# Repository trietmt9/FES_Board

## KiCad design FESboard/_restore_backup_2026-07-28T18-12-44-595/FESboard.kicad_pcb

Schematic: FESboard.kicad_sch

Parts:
C1, C2, C3, C4: 22nF; C_0402_1005Metric
C5, C6, C7, C8, C9, C10, C11, C12: 2.2nF; C_0402_1005Metric
C13, C15, C16, C22, C26: 10uF; C_0603_1608Metric
C14, C30, C34: 1uF; C_0603_1608Metric
C17: 22uF; C_0402_1005Metric
C18, C20, C21, C24, C32, C42, C60, C61, C62: 1uF; C_0402_1005Metric
C19, C23, C27, C29, C31: 0.1uF; C_0402_1005Metric
C25: 0.1uF; C_0603_1608Metric
C28: 3.3nF; C_0603_1608Metric
C33: 1.5nF; C_0402_1005Metric
C35: 22uF; C_0603_1608Metric_Pad1.08x0.95mm_HandSolder
C36: 4.7uF; C_0402_1005Metric
C37, C38, C39, C40, C41, C43, C44, C45, C47, C48, C49, C52, C54, C55, C56, C57, C58, C59, C63: 100nF; C_0402_1005Metric
C46, C50: 8pF; C_0402_1005Metric
C51, C53: 2.2uF; C_0402_1005Metric
C64: 47uF; C_0805_2012Metric
D1, D2, D3, D4, D5, D6, D7, D8: BAV99; SOT-23
D9, D10: LED; LED_0603_1608Metric
F1: Fuse; Fuse_0603_1608Metric
J1, J2, J3, J4: AudioJack4; Jack_3.5mm_PJ320D_Horizontal
J5: USB_C_Receptacle_USB2.0_16P; USB_C_Receptacle_GCT_USB4105-xx-A_16P_TopMnt_Horizontal
J6: Conn_01x02_Pin; JST_PH_S2B-PH-K_1x02_P2.00mm_Horizontal
J7, J8: Conn_ARM_SWD_TagConnect_TC2030-NL; Tag-Connect_TC2030-IDC-NL_2x03_P1.27mm_Vertical
L1: 2.2uH; L_0603_1608Metric
R1, R2, R3, R4: 10k; R_0603_1608Metric
R5: 30k; R_0402_1005Metric
R6, R7, R8, R9, R10, R11, R12, R13: 4.7k; R_0402_1005Metric
R14, R15, R23: 1M; R_0402_1005Metric
R16: 1.13k; R_0402_1005Metric
R17: 3.6k; R_0402_1005Metric
R18, R19: 5.1k; R_0402_1005Metric
R20, R21: 1k; R_0402_1005Metric
R22, R24, R25, R29, R30, R31, R32, R33: 10k; R_0402_1005Metric
R26, R28: 100k; R_0603_1608Metric
R27: 316k; R_0603_1608Metric
R34: 51k; R_0402_1005Metric
R35: 100k; R_0402_1005Metric
U1: BQ24074RGT; VQFN-16-1EP_3x3mm_P0.5mm_EP1.6x1.6mm
U2: ADS1298xPAG; TQFP-64_10x10mm_P0.5mm
U3: TPS62130A; VQFN-16-1EP_3x3mm_P0.5mm_EP1.68x1.68mm_ThermalVias
U4: TPS7A20xxxDBV; SOT-23-5
U5: ICM-42688-P; PQFN50P300X250X97-14N; PARTREV 1.2
U6: STM32F767ZITx; LQFP-144_20x20mm_P0.5mm
U7: WT02C40C
Y1: 8MHz; Crystal_SMD_3225-4Pin_3.2x2.5mm

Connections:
+3.3V: C31.1, C32.1, C35.1, C36.1, C37.1, C38.1, C39.1, C40.1, C41.1, C42.1, C43.1, C44.1, C45.1, C47.1, C49.1, C52.1, C54.1, C55.1, C56.1, C57.1, C58.1, C59.1, C60.1, C61.1, C62.1, C63.1, C64.1, J7.1 (VCC), J8.1 (VCC), L1.2, R24.1, R25.1, R26.1, R27.1, R29.1, R30.1, R31.1, R32.1, U2.48 (DVDD), U2.50 (DVDD), U3.14 (VOS), U5.5 (VDDIO), U5.8 (VDD), U6.6 (VBAT), U6.17 (VDD), U6.30 (VDD), U6.32 (VREF+), U6.33 (VDDA), U6.39 (VDD), U6.52 (VDD), U6.62 (VDD), U6.72 (VDD), U6.84 (VDD), U6.95 (VDDUSB), U6.108 (VDD), U6.121 (VDDSDMMC), U6.131 (VDD), U6.143 (PDR_ON), U6.144 (VDD), U7.9 (VDD), U7.17 (VBAT-3V6), U7.F4 (F4/VDDH)
+3.3VA: C24.1, C27.1, C29.2, C34.1, D1.2 (A), D2.2 (A), D3.2 (A), D4.2 (A), D5.2 (A), D6.2 (A), D7.2 (A), D8.2 (A), U2.19 (AVDD), U2.21 (AVDD), U2.22 (AVDD), U2.54 (AVDD1), U2.56 (AVDD), U2.59 (AVDD), U4.5 (OUT)
/IN1N: C1.1, C5.2, D3.3 (K), R6.2, U2.15 (IN1N)
/IN1P: C1.2, C6.1, D4.3 (K), R7.1, U2.16 (IN1P)
/IN2N: C2.1, C7.2, D1.3 (K), R8.2, U2.13 (IN2N)
/IN2P: C2.2, C8.1, D2.3 (K), R9.1, U2.14 (IN2P)
/IN3N: C3.1, C9.2, D7.3 (K), R10.2, U2.11 (IN3N)
/IN3P: C3.2, C10.1, D8.3 (K), R11.1, U2.12 (IN3P)
/IN4N: C4.1, C11.2, D5.3 (K), R12.2, U2.9 (IN4N)
/IN4P: C4.2, C12.1, D6.3 (K), R13.1, U2.10 (IN4P)
/OSC_IN: C46.1, U6.23 (PH0), Y1.1
/OSC_OUT: C50.1, U6.24 (PH1), Y1.3
/RLDOUT: C33.2, R1.2, R2.2, R3.2, R4.2, R23.2, U2.62 (RLDIN), U2.63 (RLDOUT)
/STM32_ADS_START: R25.2, U2.38 (START), U6.47 (PB1)
/STM32_IMU_INT1: U5.4 (INT1/INT), U6.73 (PB12)
/STM32_IMU_INT2: U5.9 (INT2/FSYNC/CLKIN), U6.78 (PD9)
/STM32_MISO: U2.43 (DOUT), U6.42 (PA6)
/STM32_MOSI: U2.34 (DIN), U6.43 (PA7)
/STM32_NRF_UART_RX: U6.37 (PA3), U7.11 (P009)
/STM32_NRF_UART_TX: U6.36 (PA2), U7.12 (P011)
/STM32_SCLK: U2.40 (SCLK), U6.41 (PA5)
/STM32_SPI2_MISO: U5.1 (AP_SDO/AP_AD0), U6.75 (PB14)
/STM32_SPI2_MOSI: U5.14 (AP_SDA/AP_SDIO/AP_SDI), U6.76 (PB15)
/STM32_SPI2_SCK: U5.13 (AP_SCL/AP_SCLK), U6.74 (PB13)
/SWCLK: J8.4 (SWCLK), U6.109 (PA14)
/SWDIO: J8.2 (SWDIO), U6.105 (PA13)
/USB_DN: J5.A7 (D-), J5.B7 (D-), U6.103 (PA11)
/USB_DP: J5.A6 (D+), J5.B6 (D+), U6.104 (PA12)
/~RST: C48.1, J8.3 (~RESET), R32.2, U6.25 (NRST)
/~STM32_ADS_CS: U2.39 (~CS), U6.40 (PA4)
/~STM32_ADS_DRDY: R29.2, U2.47 (~DRDY), U6.44 (PC4)
/~STM32_ADS_PWDWN: R30.2, U2.35 (~PWDN), U6.45 (PC5)
/~STM32_ADS_RESET: R31.2, U2.36 (~RESET), U6.46 (PB0)
/~STM32_IMU_CS: U5.12 (AP_CS), U6.77 (PD8)
GND: C13.2, C14.2, C15.2, C16.2, C17.2, C18.2, C19.2, C20.2, C21.2, C22.2, C25.2, C28.2, C31.2, C32.2, C35.2, C36.2, C37.2, C38.2, C39.2, C40.2, C41.2, C42.2, C43.2, C44.2, C45.2, C46.2, C47.2, C48.2, C49.2, C50.2, C51.2, C52.2, C53.2, C54.2, C55.2, C56.2, C57.2, C58.2, C59.2, C60.2, C61.2, C62.2, C63.2, C64.2, J5.A1 (GND), J5.A12 (GND), J5.B1 (GND), J5.B12 (GND), J5.SH (SHIELD), J6.1, J7.5 (GND), J8.5 (GND), R5.1, R14.1, R16.1, R17.1, R18.1, R19.1, R22.1, R28.2, R33.1, R35.2, U1.4 (~CE), U1.8 (VSS), U1.17 (VSS), U2.31 (RESV1), U2.33 (DGND), U2.41 (DAISY_IN), U2.49 (DGND), U2.51 (DGND), U3.6 (GND), U3.7 (FSW), U3.8 (DEF), U3.15 (GND), U3.16 (GND), U3.17 (GND), U5.6 (GND), U5.7 (RESV_7), U6.16 (VSS), U6.31 (VSSA), U6.38 (VSS), U6.51 (VSS), U6.61 (VSS), U6.83 (VSS), U6.94 (VSS), U6.107 (VSS), U6.120 (VSS), U6.130 (VSS), U7.10 (GND), U7.A0 (A0/VSS1), U7.B0 (B0/VSS2), U7.C0 (C0/VSS3), U7.D0 (D0/VSS4), U7.H0 (H0/GND), U7.H1 (H1/GND), U7.H2 (H2/GND), U7.H3 (H3/GND), Y1.2 (G), Y1.4 (G)
GNDA: C5.1, C6.2, C7.1, C8.2, C9.1, C10.2, C11.1, C12.2, C23.2, C24.2, C26.2, C27.2, C29.1, C30.2, C34.2, D1.1 (K), D2.1 (K), D3.1 (K), D4.1 (K), D5.1 (K), D6.1 (K), D7.1 (K), D8.1 (K), J1.R2, J2.R2, J3.R2, J4.R2, U2.20 (AVSS), U2.23 (AVSS), U2.25 (VREFN), U2.32 (AVSS), U2.53 (AVSS1), U2.57 (AVSS), U2.58 (AVSS), U4.2 (GND)
unnamed: D9.2 (A), R20.2
unnamed: D9.1 (K), U1.9 (~CHG)
unnamed: D10.2 (A), R21.2
unnamed: D10.1 (K), U1.7 (~PGOOD)
unnamed: F1.1, J5.A4 (VBUS), J5.A9 (VBUS), J5.B4 (VBUS), J5.B9 (VBUS)
unnamed: J1.R1, R6.1
unnamed: J1.S, R1.1
unnamed: J1.T, R7.2
unnamed: J2.R1, R8.1
unnamed: J2.S, R2.1
unnamed: J2.T, R9.2
unnamed: J3.R1, R10.1
unnamed: J3.S, R3.1
unnamed: J3.T, R11.2
unnamed: J4.R1, R12.1
unnamed: J4.S, R4.1
unnamed: J4.T, R13.2
unnamed: J5.A5 (CC1), R18.2
unnamed: J5.B5 (CC2), R19.2
unnamed: C16.1, J6.2, U1.2 (BAT), U1.3 (BAT)
unnamed: J7.4 (SWCLK), U7.15 (SWCLK)
unnamed: J7.2 (SWDIO), U7.16 (SWDIO)
unnamed: J7.3 (~RESET), U7.14 (RESET)
unnamed: L1.1, U3.1 (SW), U3.2 (SW), U3.3 (SW)
unnamed: R14.2, U1.6 (EN1)
unnamed: R15.2, U1.5 (EN2)
unnamed: R16.2, U1.12 (ILIM)
unnamed: R17.2, U1.16 (ISET)
unnamed: R5.2, U1.14 (TMR)
unnamed: R22.2, U1.1 (TS)
unnamed: R24.2, U2.52 (CLKSEL)
unnamed: C33.1, R23.1, U2.61 (RLDINV)
unnamed: C17.1, U2.28 (VCAP1)
unnamed: C18.1, U2.30 (VCAP2)
unnamed: C19.1, C20.1, U2.55 (VCAP3)
unnamed: C21.1, U2.26 (VCAP4)
unnamed: C23.1, C26.1, U2.24 (VREFP)
unnamed: R27.2, R28.1, U3.5 (FB)
unnamed: R26.2, U3.4 (PG)
unnamed: C28.1, U3.9 (SS/TR)
unnamed: R33.2, U6.138 (BOOT0)
unnamed: R34.2, R35.1, U6.101 (PA9)
unnamed: C51.1, U6.71 (VCAP_1)
unnamed: C53.1, U6.106 (VCAP_2)
VBUS: C13.1, C14.1, F1.2, R15.1, R34.1, U1.13 (IN)
VCC: C15.1, C22.1, C25.1, C30.1, R20.1, R21.1, U1.10 (OUT), U1.11 (OUT), U3.10 (VIN), U3.11 (VIN), U3.12 (VIN), U3.13 (EN), U4.1 (IN), U4.3 (EN)

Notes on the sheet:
Jack 3.5 input
STM32F767ZIT6 (Microcontrolelr Unit)
POWER
IoT (nRF53480 + nRF7002 module)
ADS1294 chip
IMU
Buck 5V -> 3.3V
USB battery charger
3.3V LDO
USB C
ADS1294

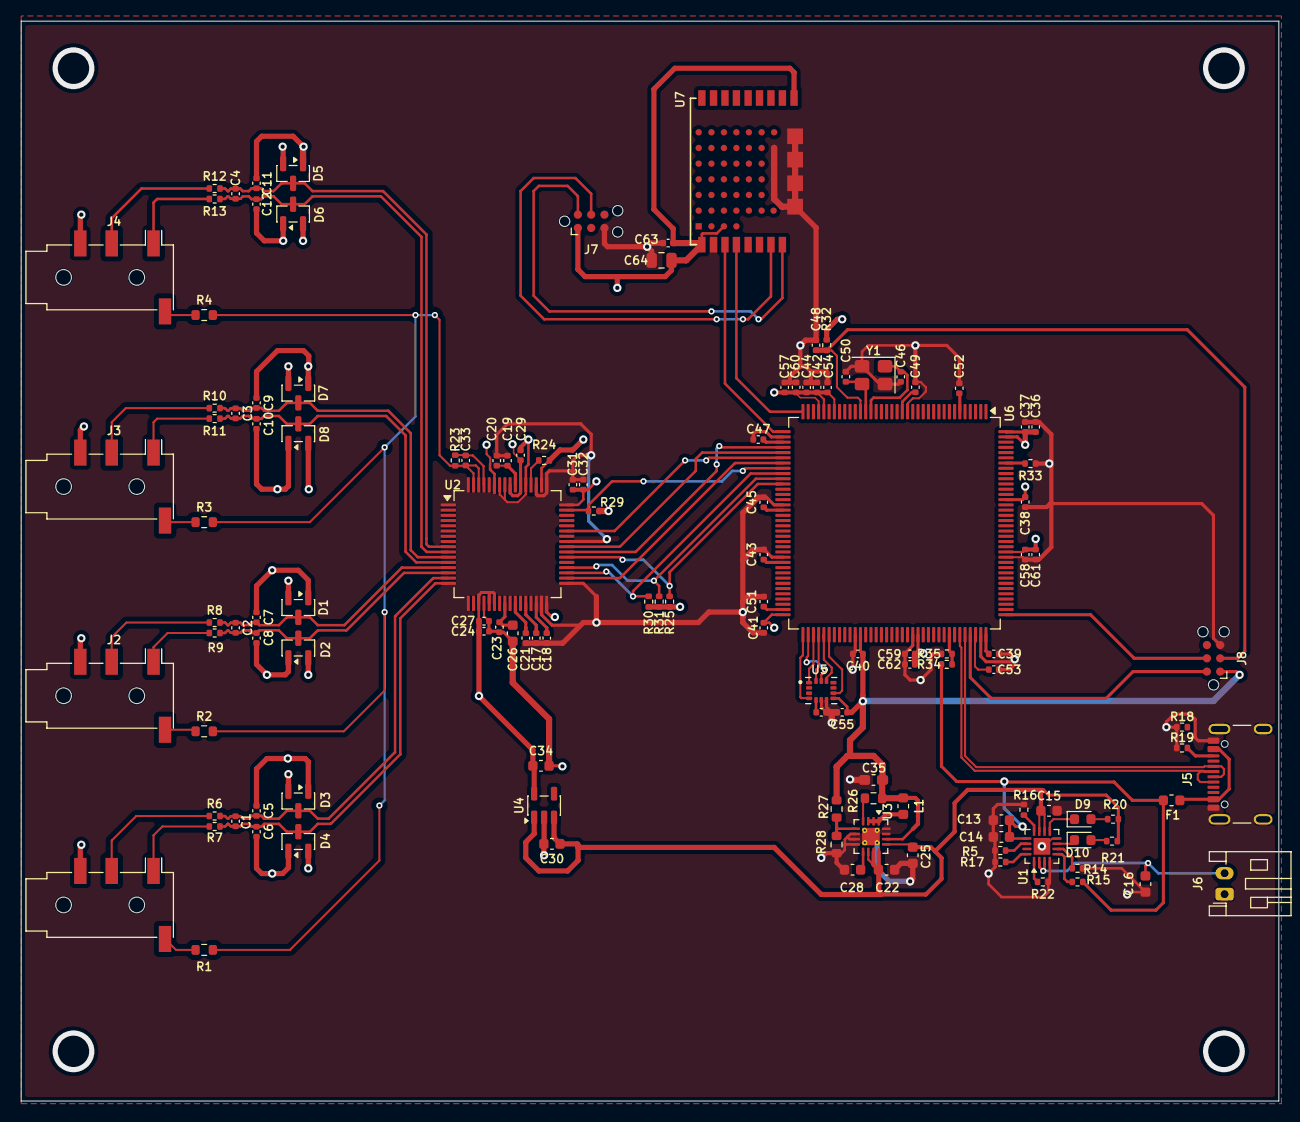
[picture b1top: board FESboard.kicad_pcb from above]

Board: 4 copper layers, 120.2 x 103.2 mm, 127 parts (0 on the bottom side), 82 nets.

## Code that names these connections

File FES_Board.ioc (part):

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Mcu.Name=STM32F767ZITx
Mcu.Package=LQFP144
Mcu.UserName=STM32F767ZITx
PA4.Signal=GPIO_Output
PA5.Mode=Full_Duplex_Master
PA5.Signal=SPI1_SCK
PA6.Mode=Full_Duplex_Master
PA6.Signal=SPI1_MISO
PA7.Mode=Full_Duplex_Master
PA7.Signal=SPI1_MOSI
PB12.Signal=GPIO_Output
PB13.Mode=Full_Duplex_Master
PB13.Signal=SPI2_SCK
PB14.Mode=Full_Duplex_Master
PB14.Signal=SPI2_MISO
PB15.Mode=Full_Duplex_Master
PB15.Signal=SPI2_MOSI
PC4.Signal=GPXTI4
PD8.Signal=GPXTI8
PH0/OSC_IN.Mode=HSE-External-Oscillator
PH0/OSC_IN.Signal=RCC_OSC_IN
PH1/OSC_OUT.Mode=HSE-External-Oscillator
PH1/OSC_OUT.Signal=RCC_OSC_OUT
RCC.HSE_VALUE=8000000
RCC.SYSCLKFreq_VALUE=108000000
RCC.SYSCLKSource=RCC_SYSCLKSOURCE_PLLCLK
board=custom

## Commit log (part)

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2026-05-21 DESIGN: ADS1298
2026-05-21 ADD: Switching Diode
2026-06-29 ADD: Power
